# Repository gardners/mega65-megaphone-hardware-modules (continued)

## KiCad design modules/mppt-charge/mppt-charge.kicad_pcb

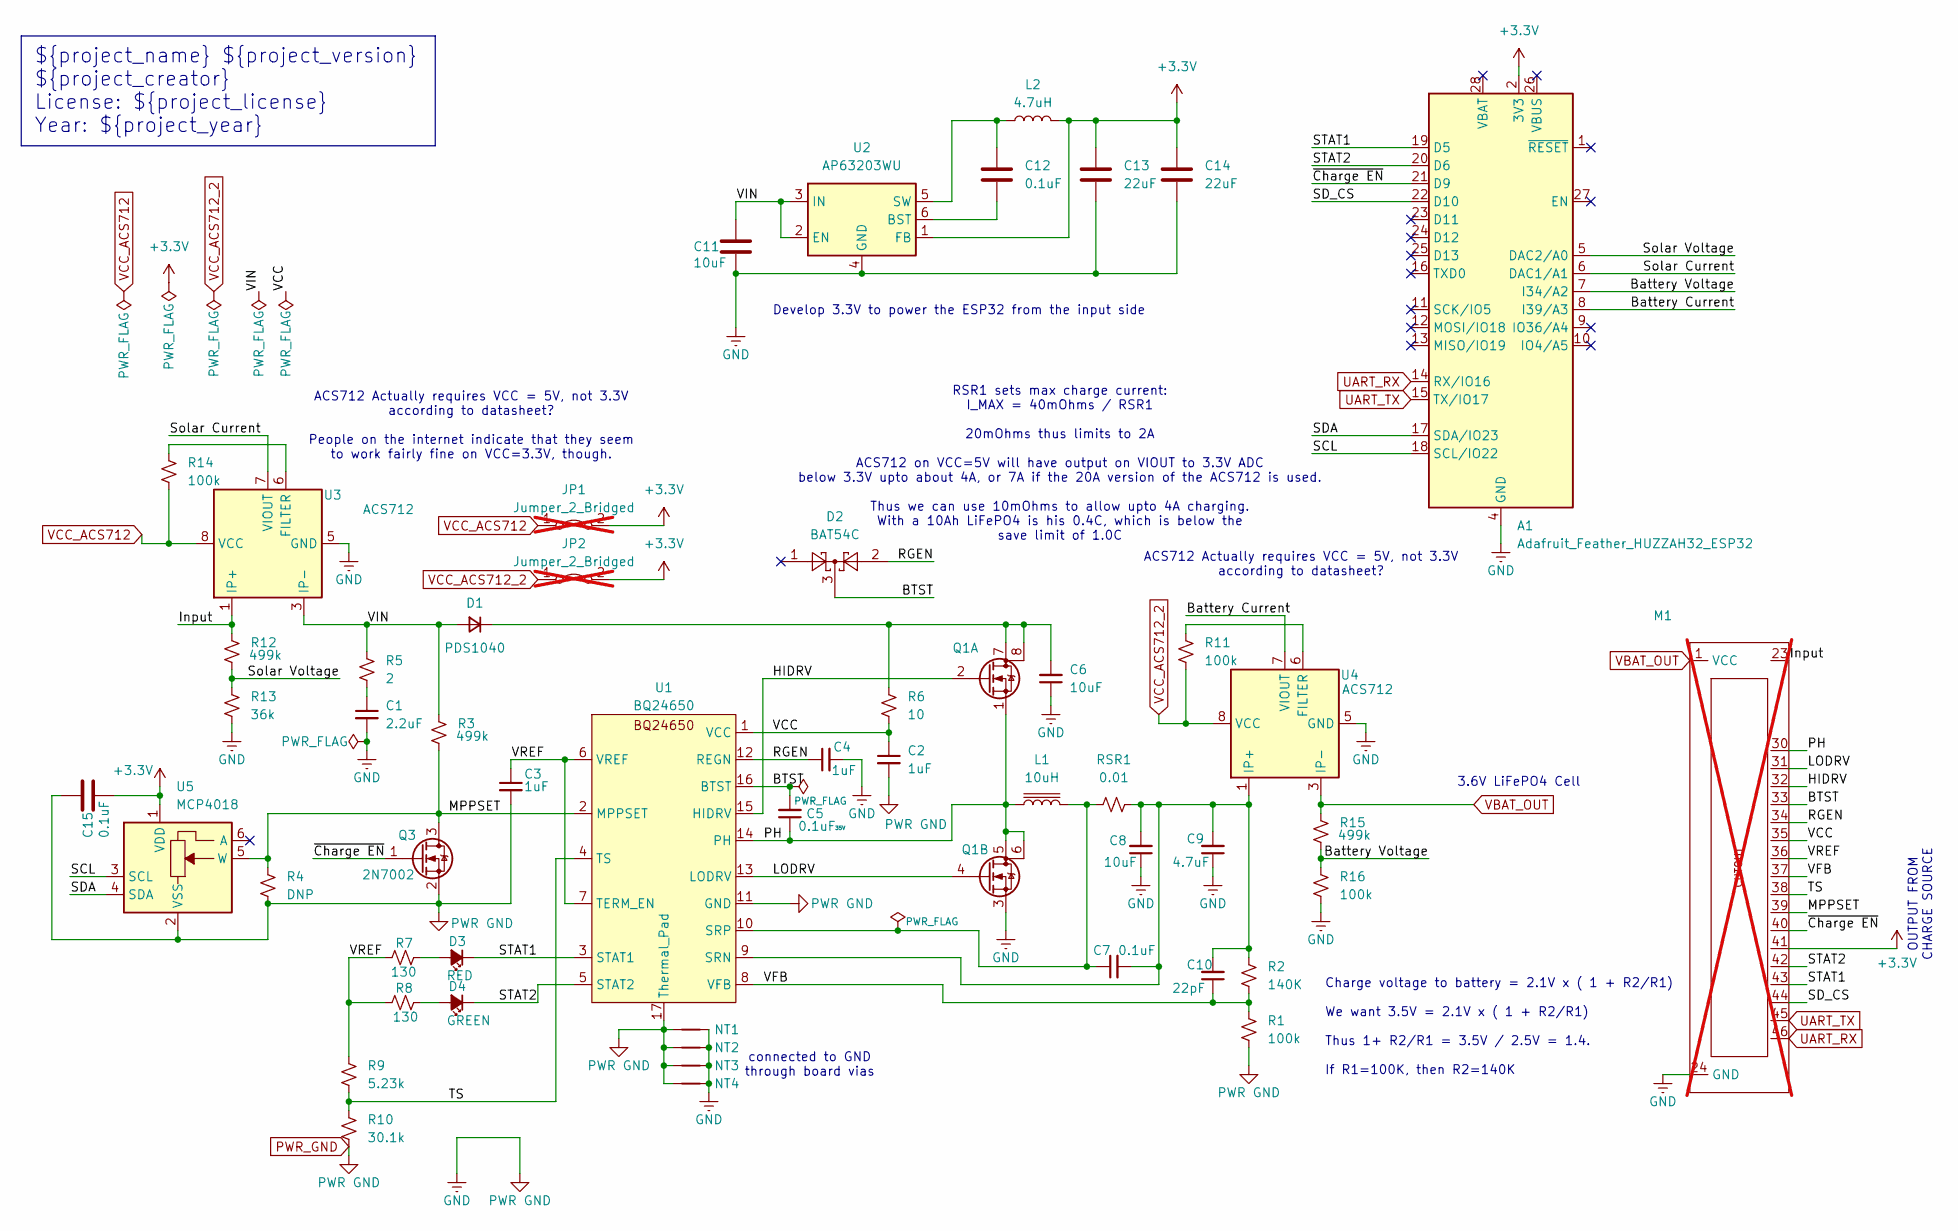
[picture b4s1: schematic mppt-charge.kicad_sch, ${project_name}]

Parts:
A1: Adafruit_Feather_HUZZAH32_ESP32; Adafruit_Feather; Mouser 485-4172
C1: 2.2uF; C_1210_3225Metric
C2, C3, C4: 1uF; C_0603_1608Metric
C5: 0.1uF; C_0603_1608Metric; Voltage Rating 35V
C6, C8: 10uF; C_1206_3216Metric
C7, C12, C15: 0.1uF; C_0603_1608Metric
C9: 4.7uF; C_0805_2012Metric
C10: 22pF; C_0603_1608Metric
C11: 10uF; C_0603_1608Metric
C13, C14: 22uF; C_0603_1608Metric; Mouser 621-PDS1040-13
D1: PDS1040; D_PowerDI-5; Mouser 583-BAT54C
D2: BAT54C; SOT-23; Mouser 583-BAT54C
D3: RED; LED_0603_1608Metric
D4: GREEN; LED_0603_1608Metric
JP1, JP2: Jumper_2_Bridged; SolderJumper-2_P1.3mm_Bridged_RoundedPad1.0x1.5mm; not fitted
L1: 10uH; L_Vishay_6.9x6.5; Mouser 70-IHLM2525CZER100M0
L2: 4.7uH; L_Vishay_IFSC-1515AH_4x4x1.8mm; Mouser 70-IFSC1515AHER4R7M0
M1: MegaCastle2x24-Module-I40.0x56.2-M80000307FFFC-SPAREPAD; not fitted
NT1, NT2, NT3, NT4: NetTie-2_SMD_Pad0.5mm
Q1: SI7272DP; PowerPAK_SO-8_Dual; Mouser 781-SI7272DP-GE3
Q3: 2N7002; SOT-23; Mouser 637-2N7002
R1, R11, R14, R16: 100k; R_0603_1608Metric
R2: 140K; R_0603_1608Metric
R3, R12, R15: 499k; R_0603_1608Metric
R4: DNP; R_0603_1608Metric
R5: 2; R_2512_6332Metric; Mouser 71-CRCW25122R00FKTG
R6: 10; R_0603_1608Metric
R7, R8: 130; R_0603_1608Metric
R9: 5.23k; R_0603_1608Metric
R10: 30.1k; R_0603_1608Metric
R13: 36k; R_0603_1608Metric
RSR1: 0.01; R_1206_3216Metric; Mouser 755-PMR18EZPFU10L0
U1: BQ24650; VQFN-16_EP_3.5x3.5_Pitch0.5mm; Mouser 595-BQ24650RVAR
U2: AP63203WU; TSOT-23-6; Mouser 621-AP63203QWU-7
U3, U4: ACS712; SOIC-8_3.9x4.9mm_P1.27mm; Mouser 250-71240LLCBTR010B3
U5: MCP4018; SOT-363_SC-70-6; Mouser 579-MCP4018T103ELTY

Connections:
+3.3V: A1.2 (3V3), C13.1, C14.1, C15.1, JP1.2 (B), JP2.2 (B), L2.2, M1.41, U2.1 (FB), U5.1 (VDD)
/BTST: C5.2, D2.3, M1.33, U1.16 (BTST)
/Battery Current: A1.8 (I39/A3), U4.7 (VIOUT)
/Battery Voltage: A1.7 (I34/A2), R15.2, R16.1
/HIDRV: M1.32, Q1.2 (G), U1.15 (HIDRV)
/Input: M1.23, R12.1, U3.1 (IP+), U3.2 (IP+)
/LODRV: M1.31, Q1.4 (G), U1.13 (LODRV)
/MPPSET: M1.39, Q3.3 (D), R3.2, R4.1, U1.2 (MPPSET), U5.5 (W)
/PH: C5.1, L1.1, M1.30, Q1.1 (S), Q1.5 (D), Q1.6 (D), U1.14 (PH)
/RGEN: C4.1, D2.2, M1.34, U1.12 (REGN)
/SCL: A1.18 (SCL/IO22), U5.3 (SCL)
/SDA: A1.17 (SDA/IO23), U5.4 (SDA)
/SD_CS: A1.22 (D10), M1.44
/STAT1: A1.19 (D5), D3.1 (K), M1.43, U1.3 (STAT1)
/STAT2: A1.20 (D6), D4.1 (K), M1.42, U1.5 (STAT2)
/Solar Current: A1.6 (DAC1/A1), U3.7 (VIOUT)
/Solar Voltage: A1.5 (DAC2/A0), R12.2, R13.1
/TS: M1.38, R9.2, R10.1, U1.4 (TS)
/VCC: C2.1, M1.35, R6.2, U1.1 (VCC)
/VFB: C10.1, M1.37, R1.1, R2.2, U1.8 (VFB)
/VIN: C11.2, D1.2 (A), R3.1, R5.1, U2.2 (EN), U2.3 (IN), U3.3 (IP-), U3.4 (IP-)
/VREF: C3.1, M1.36, R7.1, R8.1, R9.1, U1.6 (VREF), U1.7 (TERM_EN)
/~Charge EN: A1.21 (D9), M1.40, Q3.1 (G)
unnamed: C1.1, R5.2
unnamed: C6.2, D1.1 (K), Q1.7 (D), Q1.8 (D), R6.1
unnamed: D3.2 (A), R7.2
unnamed: D4.2 (A), R8.2
unnamed: C7.2, C8.2, C9.2, C10.2, R2.1, RSR1.1, U1.9 (SRN), U4.1 (IP+), U4.2 (IP+)
unnamed: C7.1, L1.2, RSR1.2, U1.10 (SRP)
unnamed: C12.2, U2.6 (BST)
unnamed: C12.1, L2.1, U2.5 (SW)
unnamed: R14.1, U3.6 (FILTER)
unnamed: R11.1, U4.6 (FILTER)
PWR_GND: A1.4 (GND), C1.2, C2.2, C3.2, C4.2, C6.1, C8.1, C9.1, C11.1, C13.2, C14.2, C15.2, M1.24 (GND), NT1.1, NT1.2, NT2.1, NT2.2, NT3.1, NT3.2, NT4.1, NT4.2, Q1.3 (S), Q3.2 (S), R1.2, R4.2, R10.2, R13.2, R16.2, U1.11 (GND), U1.17 (Thermal_Pad), U2.4 (GND), U3.5 (GND), U4.5 (GND), U5.2 (VSS)
UART_RX: A1.14 (RX/IO16), M1.46
UART_TX: A1.15 (TX/IO17), M1.45
VBAT_OUT: M1.1 (VCC), R15.1, U4.3 (IP-), U4.4 (IP-)
VCC_ACS712: JP1.1 (A), R14.2, U3.8 (VCC)
VCC_ACS712_2: JP2.1 (A), R11.2, U4.8 (VCC)

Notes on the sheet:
ACS712 Actually requires VCC = 5V, not 3.3V according to datasheet?
ACS712 Actually requires VCC = 5V, not 3.3V according to datasheet? People on the internet indicate that they seem to work fairly fine on VCC=3.3V, though.
3.6V LiFePO4 Cell
${project_name} ${project_version} ${project_creator} License: ${project_license} Year: ${project_year}
OUTPUT FROM CHARGE SOURCE
Charge voltage to battery = 2.1V x ( 1 + R2/R1) We want 3.5V = 2.1V x ( 1 + R2/R1) Thus 1+ R2/R1 = 3.5V / 2.5V = 1.4. If R1=100K, then R2=140K
RSR1 sets max charge current: I_MAX = 40mOhms / RSR1 20mOhms thus limits to 2A ACS712 on VCC=5V will have output on VIOUT to 3.3V ADC below 3.3V upto about 4A, or 7A if the 20A version of the ACS712 is used. Thus we can use 10mOhms to allow upto 4A charging. With a 10Ah LiFePO4 is his 0.4C, which i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
connected to GND through board vias
Develop 3.3V to power the ESP32 from the input side

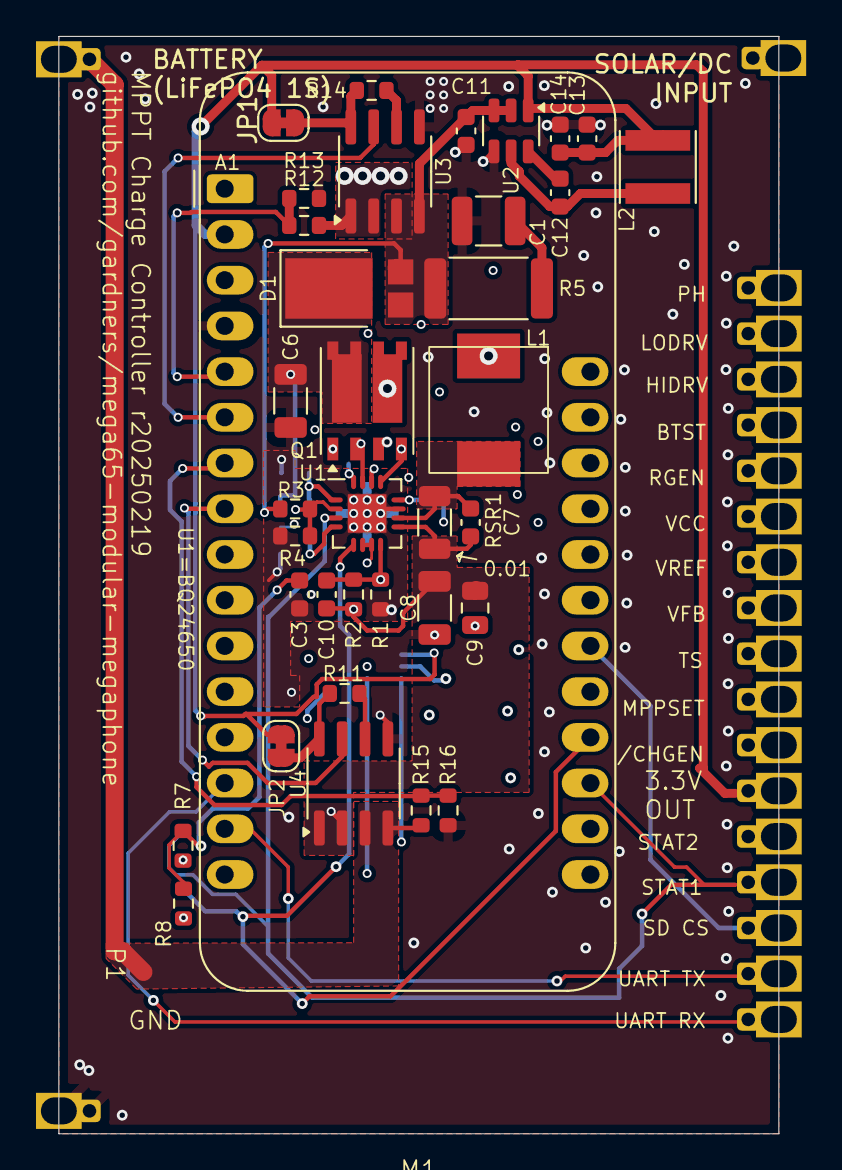
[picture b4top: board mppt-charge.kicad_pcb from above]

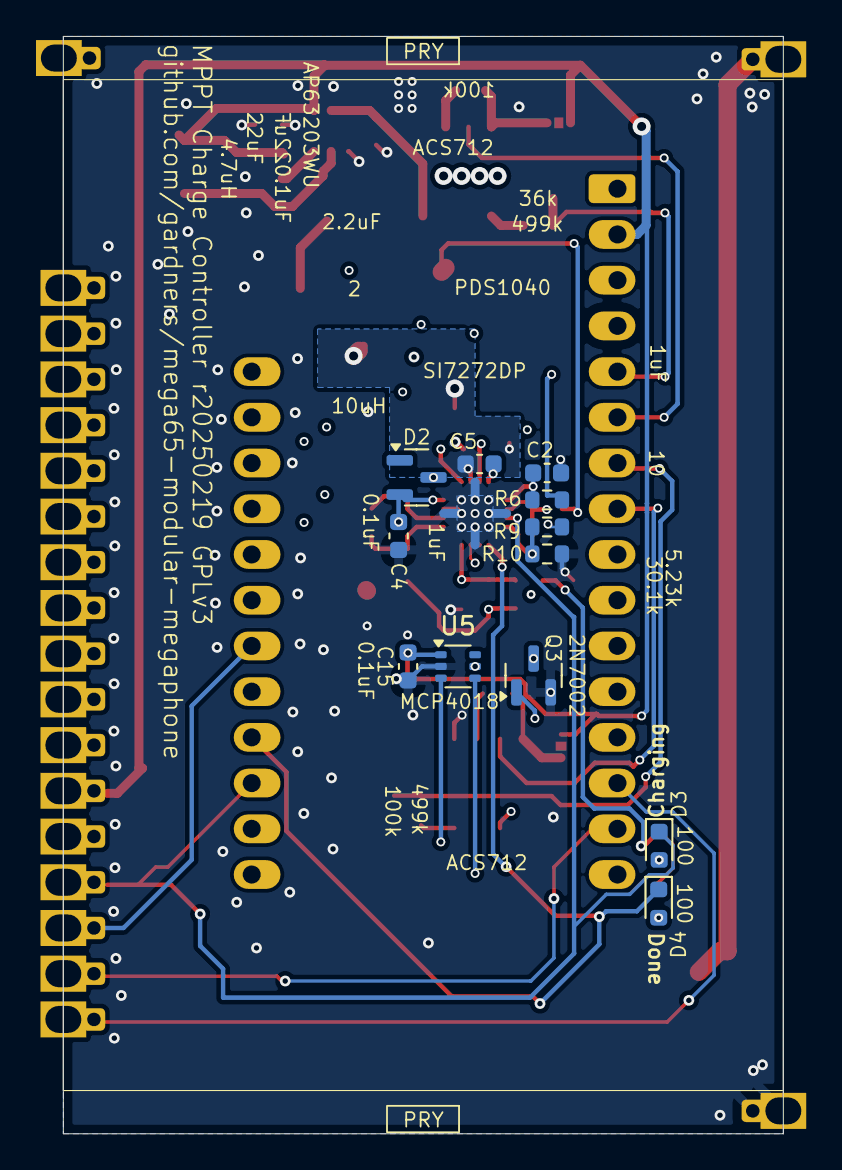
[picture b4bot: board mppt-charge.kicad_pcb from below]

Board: 4 copper layers, 40.0 x 61.0 mm, 53 parts (16 on the bottom side), 39 nets.

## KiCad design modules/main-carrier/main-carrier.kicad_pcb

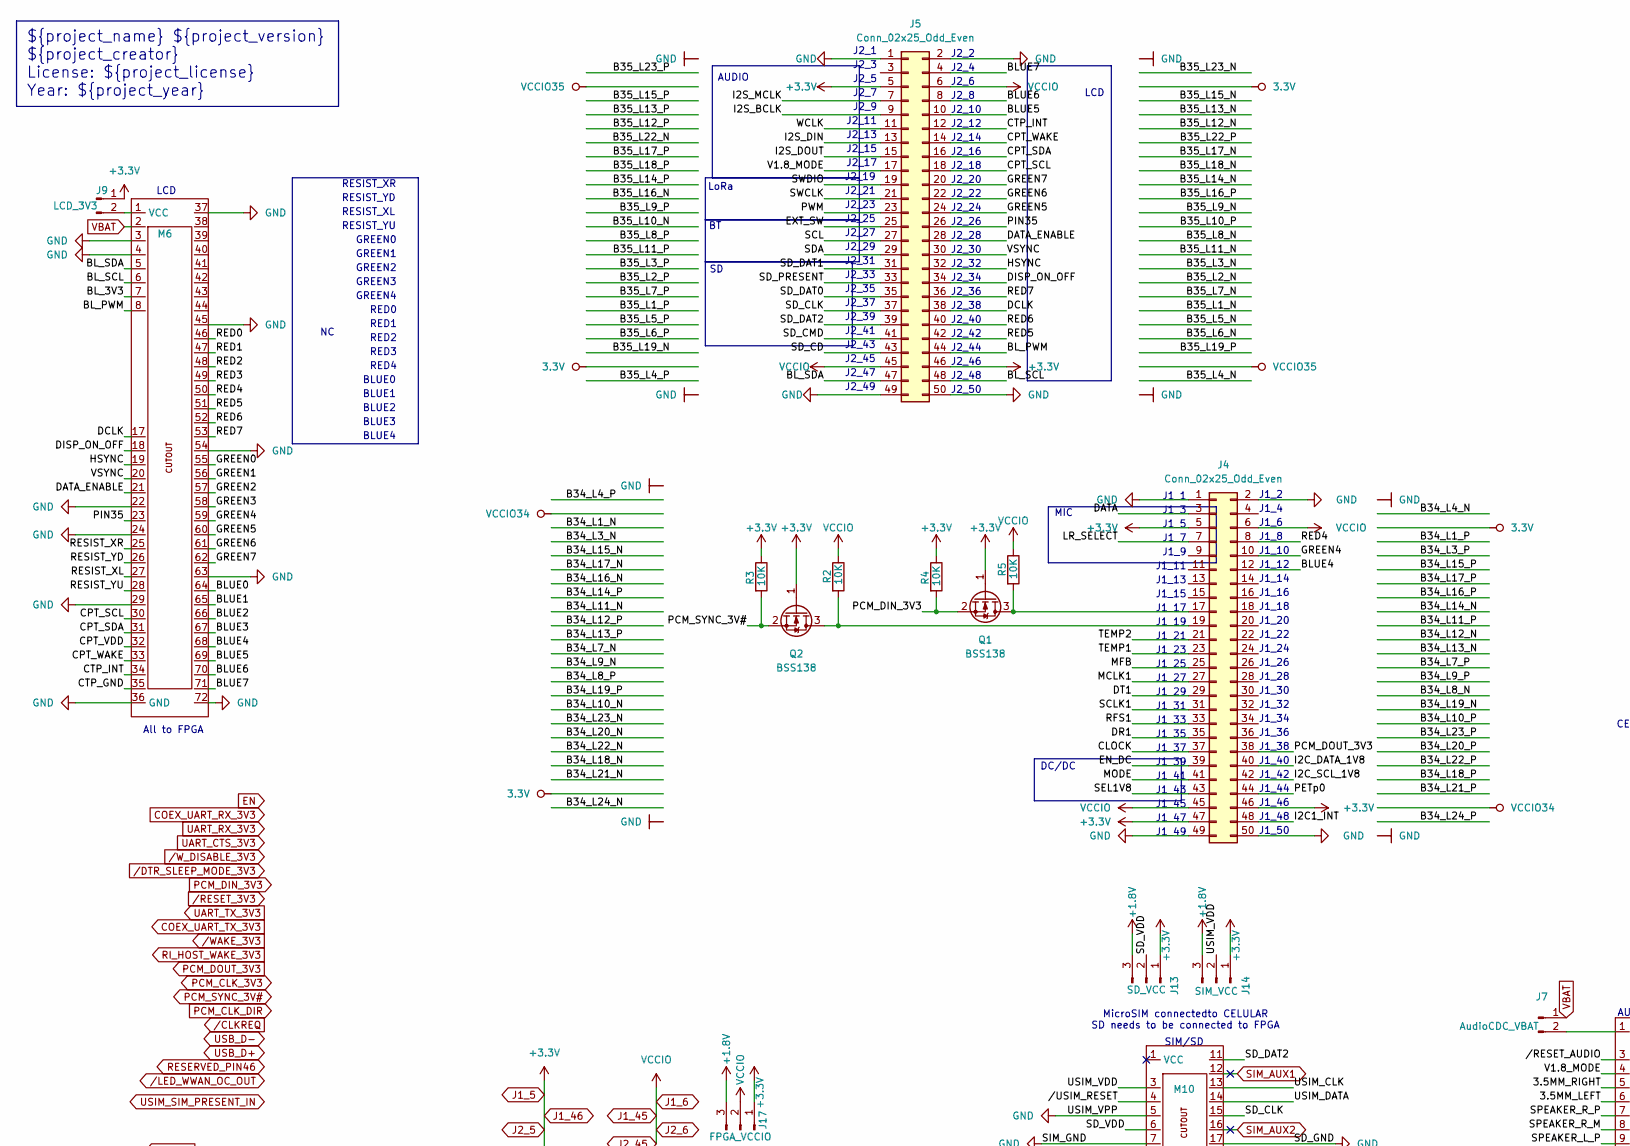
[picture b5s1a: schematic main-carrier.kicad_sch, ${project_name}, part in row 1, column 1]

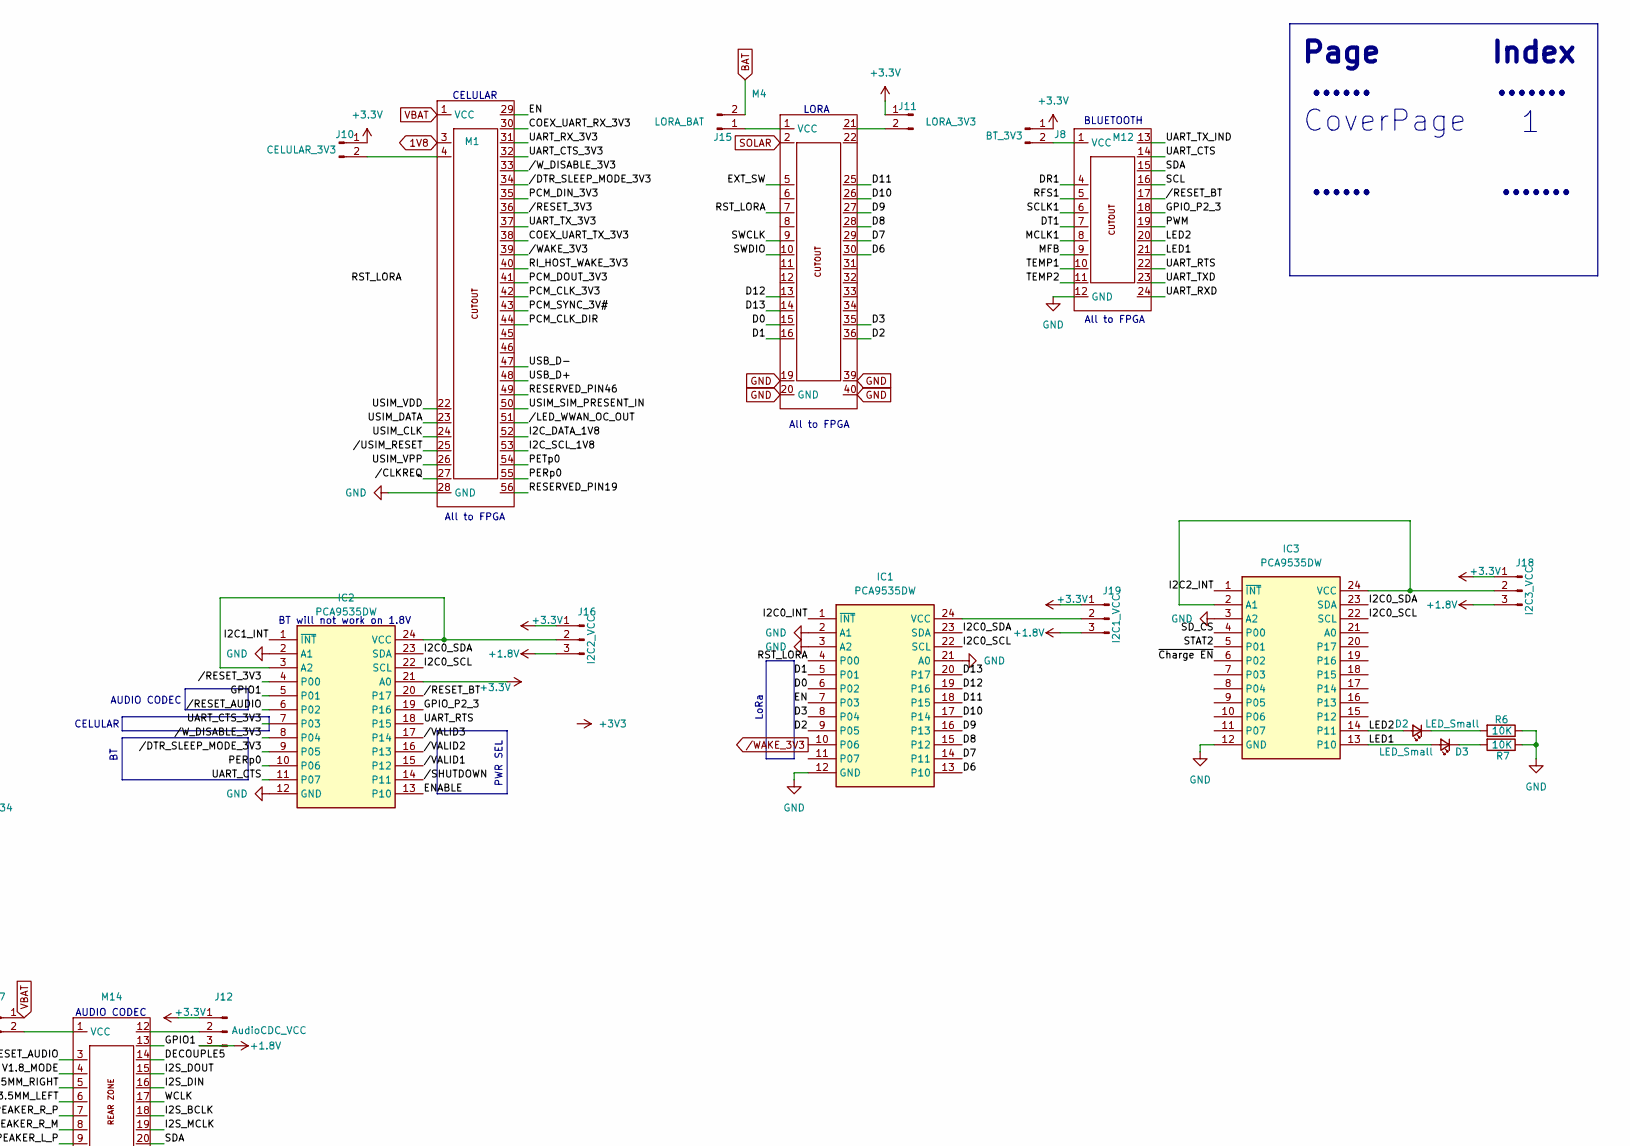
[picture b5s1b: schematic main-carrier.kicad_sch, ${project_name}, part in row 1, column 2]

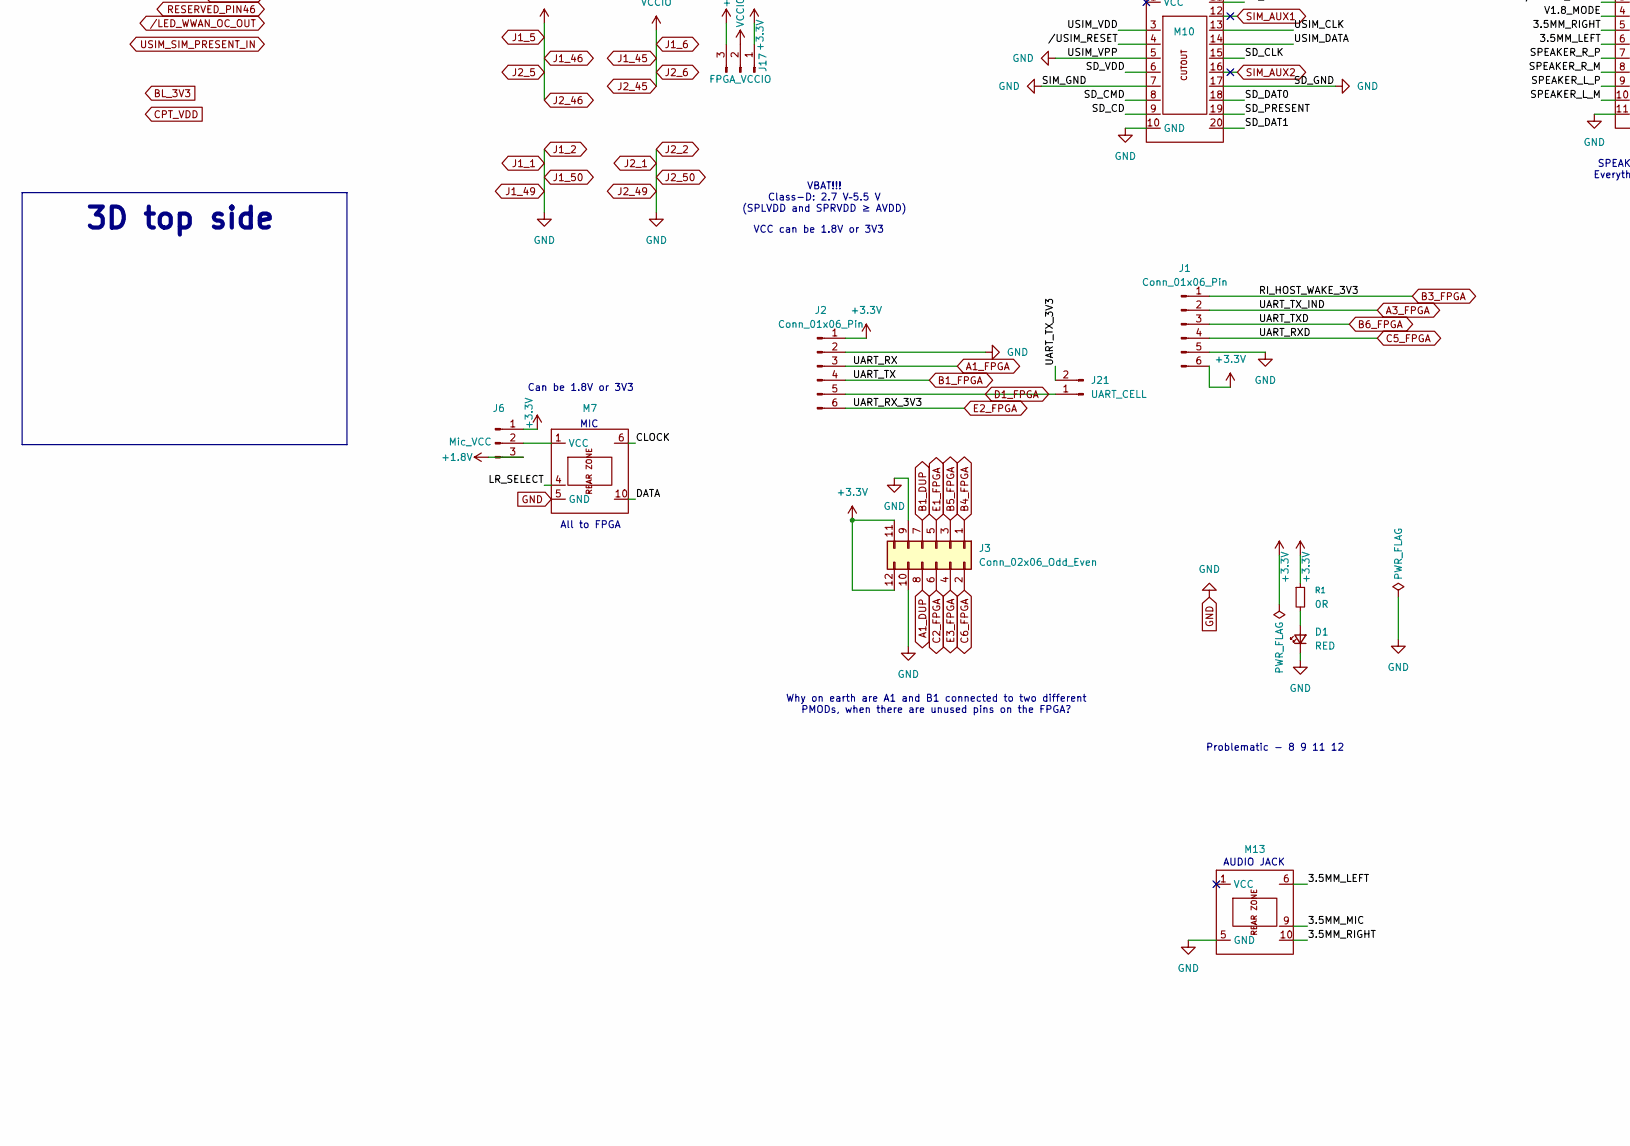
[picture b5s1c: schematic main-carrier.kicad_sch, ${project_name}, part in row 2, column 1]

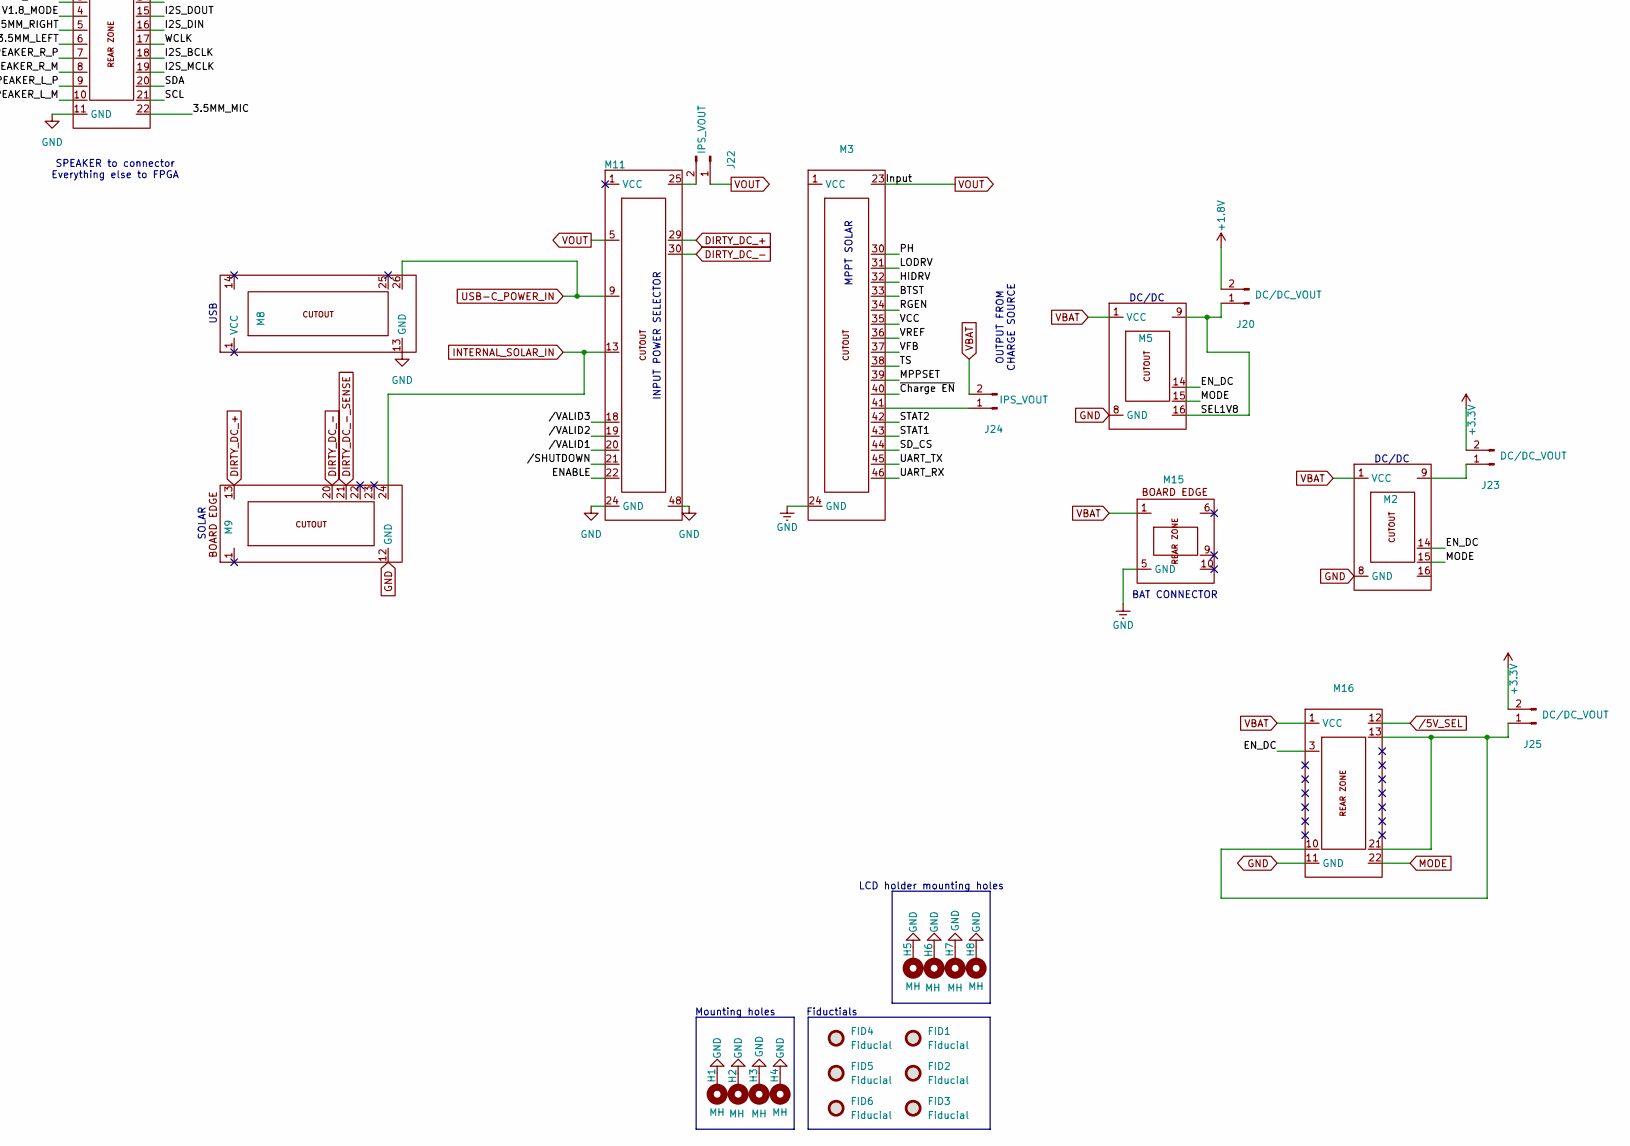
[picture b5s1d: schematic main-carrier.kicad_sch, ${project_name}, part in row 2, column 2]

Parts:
D1: RED; LED_0603_1608Metric; LCSC C965799
D2, D3: LED_Small; LED_0603_1608Metric
FID1, FID2, FID3, FID4, FID5, FID6: Fiducial; Fiducial_0.5mm_Mask1mm
H1, H2, H3, H4, H5, H6, H7, H8: MH; MountingHole_3mm_Pad
IC1, IC2, IC3: PCA9535DW; SOIC127P1030X265-24N; Mouser Part Number 595-PCA9535DW
J1, J2: Conn_01x06_Pin; PinHeader_1x06_P2.54mm_Vertical
J3: Conn_02x06_Odd_Even; PinHeader_2x06_P2.54mm_Vertical
J4, J5: Conn_02x25_Odd_Even; PinHeader_2x25_P2.54mm_Vertical
J6: Mic_VCC; PinSocket_1x03_P2.54mm_Vertical
J7: AudioCDC_VBAT; PinSocket_1x02_P2.54mm_Vertical
J8: BT_3V3; PinSocket_1x02_P2.54mm_Vertical
J9: LCD_3V3; PinSocket_1x02_P2.54mm_Vertical
J10: CELULAR_3V3; PinSocket_1x02_P2.54mm_Vertical
J11: LORA_3V3; PinSocket_1x02_P2.54mm_Vertical
J12: AudioCDC_VCC; PinSocket_1x03_P2.54mm_Vertical
J13: SD_VCC; PinSocket_1x03_P2.54mm_Vertical
J14: SIM_VCC; PinSocket_1x03_P2.54mm_Vertical
J15: LORA_BAT; PinSocket_1x02_P2.54mm_Vertical
J16: I2C2_VCC; PinSocket_1x03_P2.54mm_Vertical
J17: FPGA_VCCIO; PinSocket_1x03_P2.54mm_Vertical
J18: I2C3_VCC; PinSocket_1x03_P2.54mm_Vertical
J19: I2C1_VCC; PinSocket_1x03_P2.54mm_Vertical
J20, J23, J25: DC/DC_VOUT; PinSocket_1x02_P2.54mm_Vertical
J21: UART_CELL; PinSocket_1x02_P2.54mm_Vertical
J22, J24: IPS_VOUT; PinSocket_1x02_P2.54mm_Vertical
M1: MegaCastle2x28-I42.8x66.3-MB00007FFFFFFFF
M2, M5: MegaCastle2x8-I15.0x15.5-M8187
M3: MegaCastle2x24-I40.0x56.2-M80000307FFFC
M4: MegaCastle2x20-I40.0x46.0-MBCFFF3CFFF3
M6: MegaCastle2x36-I40.0x86.6-MFFFFFFFFFFFFFF
M7: MegaCastle2x5-I10.0x7.9-M9C4
M8: MegaCastle2x13-I20.0x28.2-M800C00C
M9: MegaCastle2x12-I20.0x25.7-M80181F
M10: MegaCastle2x10-I16.0x20.6-MBFFFF
M11: MegaCastle2x24-I47.0x56.2-M88887D8C0001
M12: MegaCastle2x12-I24.0x25.7-M9FFFFF
M13: MegaCastle2x7-I15.0x13.0-M8314
M14: MegaCastle2x11-I22.0x23.1-MBFFFFC
M15: MegaCastle2x5-I15.0x7.9-M8CC
M16: MegaCastle2x11-I15.7x23.1-MA0780C-EDGE
Q1, Q2: BSS138; SOT-23
R1: 0R; C_0402_1005Metric; LCSC C106231
R2, R3, R4, R5, R6, R7: 10K; R_0603_1608Metric

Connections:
1V8: M1.3
+1.8V: J6.3, J12.3, J13.3, J14.3, J16.3, J17.3, J18.3, J19.3, J20.2
/3.5MM_LEFT: M13.6, M14.6
/3.5MM_MIC: M13.9, M14.22
/3.5MM_RIGHT: M13.10, M14.5
/BLUE0: M6.64
/BLUE1: M6.65
/BLUE2: M6.66
/BLUE3: M6.67
/BLUE4: J4.12, M6.68
/BLUE5: J5.10, M6.69
/BLUE6: J5.8, M6.70
/BLUE7: J5.4, M6.71
/BL_PWM: J5.44, M6.8
/BL_SCL: J5.48, M6.6
/BL_SDA: J5.47, M6.5
/BTST: M3.33
/CLOCK: J4.37, M7.6
/CPT_SCL: J5.18, M6.30
/CPT_SDA: J5.16, M6.31
/CPT_WAKE: J5.14, M6.33
/CTP_GND: M6.35
/CTP_INT: J5.12, M6.34
/D0: IC1.6 (P02), M4.15
/D1: IC1.5 (P01), M4.16
/D2: IC1.9 (P05), M4.36
/D3: IC1.8 (P04), M4.35
/D6: IC1.13 (P10), M4.30
/D7: IC1.14 (P11), M4.29
/D8: IC1.15 (P12), M4.28
/D9: IC1.16 (P13), M4.27
/D10: IC1.17 (P14), M4.26
/D11: IC1.18 (P15), M4.25
/D12: IC1.19 (P16), M4.13
/D13: IC1.20 (P17), M4.14
/DATA: J4.3, M7.10
/DATA_ENABLE: J5.28, M6.21
/DCLK: J5.38, M6.17
/DECOUPLE5: M14.14
/DISP_ON_OFF: J5.34, M6.18
/DR1: J4.35, M12.4
/DT1: J4.29, M12.7
/ENABLE: IC2.13 (P10), M11.22
/EN_DC: J4.39, M2.14, M5.14, M16.3
/EXT_SW: J5.25, M4.5
/GPIO1: IC2.5 (P01), M14.13
/GPIO_P2_3: IC2.19 (P16), M12.18
/GREEN0: M6.55
/GREEN1: M6.56
/GREEN2: M6.57
/GREEN3: M6.58
/GREEN4: J4.10, M6.59
/GREEN5: J5.24, M6.60
/GREEN6: J5.22, M6.61
/GREEN7: J5.20, M6.62
/HIDRV: M3.32
/HSYNC: J5.32, M6.19
/I2C0_INT: IC1.1 (~INT)
/I2C0_SCL: IC1.22 (SCL), IC2.22 (SCL), IC3.22 (SCL)
/I2C0_SDA: IC1.23 (SDA), IC2.23 (SDA), IC3.23 (SDA)
/I2C1_INT: IC2.1 (~INT), J4.48
/I2C2_INT: IC3.1 (~INT)
/I2C_DATA_1V8: J4.40, M1.52
/I2C_SCL_1V8: J4.42, M1.53
/I2S_BCLK: J5.9, M14.18
/I2S_DIN: J5.13, M14.16
/I2S_DOUT: J5.15, M14.15
/I2S_MCLK: J5.7, M14.19
/LED1: D3.2 (A), IC3.13 (P10), M12.21
/LED2: D2.2 (A), IC3.14 (P11), M12.20
/LODRV: M3.31
/LR_SELECT: J4.7, M7.4
/MCLK1: J4.27, M12.8
/MFB: J4.25, M12.9
/MPPSET: M3.39
/PERp0: IC2.10 (P06), M1.55
/PETp0: J4.44, M1.54
/PH: M3.30
/PIN35: J5.26, M6.23
/PWM: J5.23, M12.19
/RED0: M6.46
/RED1: M6.47
/RED2: M6.48
/RED3: M6.49
/RED4: J4.8, M6.50
/RED5: J5.42, M6.51
/RED6: J5.40, M6.52
/RED7: J5.36, M6.53
/RESERVED_PIN19: M1.56
/RESIST_XL: M6.27
/RESIST_XR: M6.25
/RESIST_YD: M6.26
/RESIST_YU: M6.28
/RFS1: J4.33, M12.5
/RGEN: M3.34
/RST_LORA: IC1.4 (P00), M4.7
/SCL: J5.27, M12.16, M14.21
/SCLK1: J4.31, M12.6
/SDA: J5.29, M12.15, M14.20
/SD_CD: J5.43, M10.9
/SD_CLK: J5.37, M10.15
/SD_CMD: J5.41, M10.8
/SD_CS: IC3.4 (P00), M3.44
/SD_DAT0: J5.35, M10.18
/SD_DAT1: J5.31, M10.20
/SD_DAT2: J5.39, M10.11
/SD_PRESENT: J5.33, M10.19
/SD_VDD: J13.2, M10.6
/SEL1V8: J4.43, J20.1, M5.9, M5.16
/SPEAKER_L_M: M14.10
/SPEAKER_L_P: M14.9
/SPEAKER_R_M: M14.8
/SPEAKER_R_P: M14.7
/STAT1: M3.43
/STAT2: IC3.5 (P01), M3.42
/SWCLK: J5.21, M4.9
/SWDIO: J5.19, M4.10
/TEMP1: J4.23, M12.10
/TEMP2: J4.21, M12.11
/TS: M3.38
/UART_CTS: IC2.11 (P07), M12.14
/UART_RTS: IC2.18 (P15), M12.22
/USIM_CLK: M1.24, M10.13
/USIM_DATA: M1.23, M10.14
/USIM_VDD: J14.2, M1.22, M10.3
/V1.8_MODE: J5.17, M14.4
/VCC: M3.35
/VFB: M3.37
/VREF: M3.36
/VSYNC: J5.30, M6.20
/WCLK: J5.11, M14.17
//RESET_AUDIO: IC2.6 (P02), M14.3
//RESET_BT: IC2.20 (P17), M12.17
//SHUTDOWN: IC2.14 (P11), M11.21
//USIM_RESET: M1.25, M10.4
//VALID1: IC2.15 (P12), M11.20
//VALID2: IC2.16 (P13), M11.19
//VALID3: IC2.17 (P14), M11.18
/~Charge EN: IC3.6 (P02), M3.40
A1_DUP: J3.8
A1_FPGA: J2.3, M3.46
A3_FPGA: J1.2, M12.13
B1_DUP: J3.7
B1_FPGA: J2.4, M3.45
B3_FPGA: J1.1, M1.40
B4_FPGA: J3.1
B5_FPGA: J3.3
B6_FPGA: J1.3, M12.23
BAT: J15.2
BL_3V3: M6.7
C2_FPGA: J3.6
C5_FPGA: J1.4, M12.24
C6_FPGA: J3.2
COEX_UART_RX_3V3: M1.30
COEX_UART_TX_3V3: M1.38
CPT_VDD: M6.32
D1_FPGA: J2.5, J21.1
DIRTY_DC_+: M9.13, M11.29
DIRTY_DC_-: M9.20, M11.30
DIRTY_DC_-_SENSE: M9.21
E1_FPGA: J3.5
E2_FPGA: J2.6, M1.31
E3_FPGA: J3.4
EN: IC1.7 (P03), M1.29
GND: D1.1 (K), H1.1, H2.1, H3.1, H4.1, H5.1, H6.1, H7.1, H8.1, IC1.2 (A1), IC1.3 (A2), IC1.12 (GND), IC1.21 (A0), IC2.2 (A1), IC2.12 (GND), IC3.3 (A2), IC3.12 (GND), J1.5, J2.2, J3.9, J3.10, J4.1, J4.2, J4.49, J4.50, J5.1, J5.2, J5.49, J5.50, M1.26, M1.28 (GND), M2.8 (GND), M3.24 (GND), M4.19, M4.20 (GND), M4.39, M4.40, M5.8 (GND), M6.3, M6.4, M6.22, M6.24, M6.29, M6.36 (GND), M6.37, M6.45, M6.54, M6.63, M6.72, M7.5 (GND), M8.13 (GND), M9.12 (GND), M10.5, M10.7, M10.10 (GND), M10.17, M11.24 (GND), M11.48, M12.12 (GND), M13.5 (GND), M14.11 (GND), M15.5 (GND), M16.11 (GND), R6.1, R7.1
INTERNAL_SOLAR_IN: M9.24, M11.13
J1_45: J4.6, J4.45, J5.6, J5.45, J17.2, R2.1, R5.1
J1_46: IC2.21 (A0), J1.6, J2.1, J3.11, J3.12, J4.5, J4.46, J4.47, J5.5, J5.46, J6.1, J8.1, J9.1, J10.1, J11.1, J12.1, J13.1, J14.1, J16.1, J17.1, J18.1, J19.1, J23.2, J25.2, Q1.1 (G), Q2.1 (G), R1.1, R3.1, R4.1
MODE: J4.41, M2.15, M5.15, M16.22
unnamed: D1.2 (A), R1.2
unnamed: D2.1 (K), R6.2
unnamed: D3.1 (K), R7.2
unnamed: IC1.24 (VCC), J19.2
unnamed: IC2.3 (A2), IC2.24 (VCC), J16.2
unnamed: IC3.2 (A1), IC3.24 (VCC), J18.2
unnamed: J4.17, Q1.3 (D), R5.2
unnamed: J4.19, Q2.3 (D), R2.2
unnamed: J6.2, M7.1 (VCC)
unnamed: J7.2, M14.1 (VCC)
unnamed: J8.2, M12.1 (VCC)
unnamed: J9.2, M6.1 (VCC)
unnamed: J10.2, M1.4
unnamed: J11.2, M4.21
unnamed: J12.2, M14.12
unnamed: J15.1, M4.1 (VCC)
unnamed: J22.2, M11.25
unnamed: J23.1, M2.9
unnamed: J24.1, M3.41
unnamed: J25.1, M16.10, M16.13, M16.21
PCM_CLK_3V3: M1.42
PCM_CLK_DIR: M1.44
PCM_DIN_3V3: M1.35, Q1.2 (S), R4.2
PCM_DOUT_3V3: J4.38, M1.41
PCM_SYNC_3V#: M1.43, Q2.2 (S), R3.2
RESERVED_PIN46: M1.49
SIM_AUX1: M10.12
SIM_AUX2: M10.16
SOLAR: M4.2
UART_CTS_3V3: IC2.7 (P03), M1.32
UART_TX_3V3: J21.2, M1.37
USB-C_POWER_IN: M8.26, M11.9
USB_D+: M1.48
USB_D-: M1.47
USIM_SIM_PRESENT_IN: M1.50
VBAT: J7.1, J24.2, M1.1 (VCC), M2.1 (VCC), M5.1 (VCC), M6.2, M15.1, M16.1 (VCC)
VOUT: J22.1, M3.23, M11.5
/5V_SEL: M16.12
/CLKREQ: M1.27
/DTR_SLEEP_MODE_3V3: IC2.9 (P05), M1.34
/LED_WWAN_OC_OUT: M1.51
/RESET_3V3: IC2.4 (P00), M1.36
/WAKE_3V3: IC1.10 (P06), M1.39
/W_DISABLE_3V3: IC2.8 (P04), M1.33

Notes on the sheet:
J1_31
J1_17
J1_19
SPEAKER to connector Everything else to FPGA
AUDIO CODEC
INPUT POWER SELECTOR
J1_33
J1_24
J2_47
J1_11
RED3
J1_44
J1_21
Fiductials
BLUE3
J2_1
J2_35
SOLAR
J1_50
LoRa
BLUE0
J1_5
GREEN0
Problematic - 8 9 11 12
J2_43
PWR SEL
All to FPGA
J2_48
GREEN3
DC/DC
J1_7
J2_45
MIC
3D top side
J2_4
J1_18
J1_49
J1_15
J2_37
J1_26

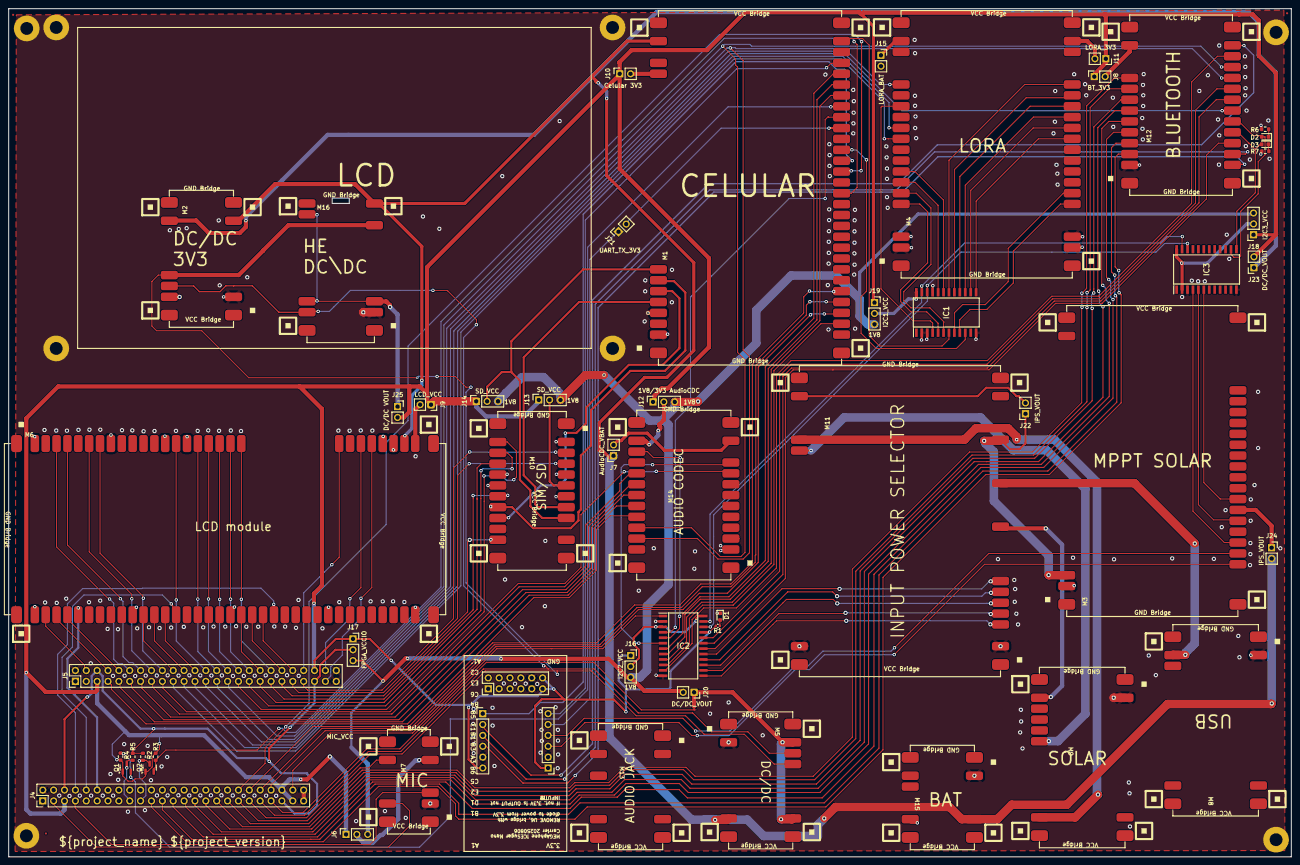
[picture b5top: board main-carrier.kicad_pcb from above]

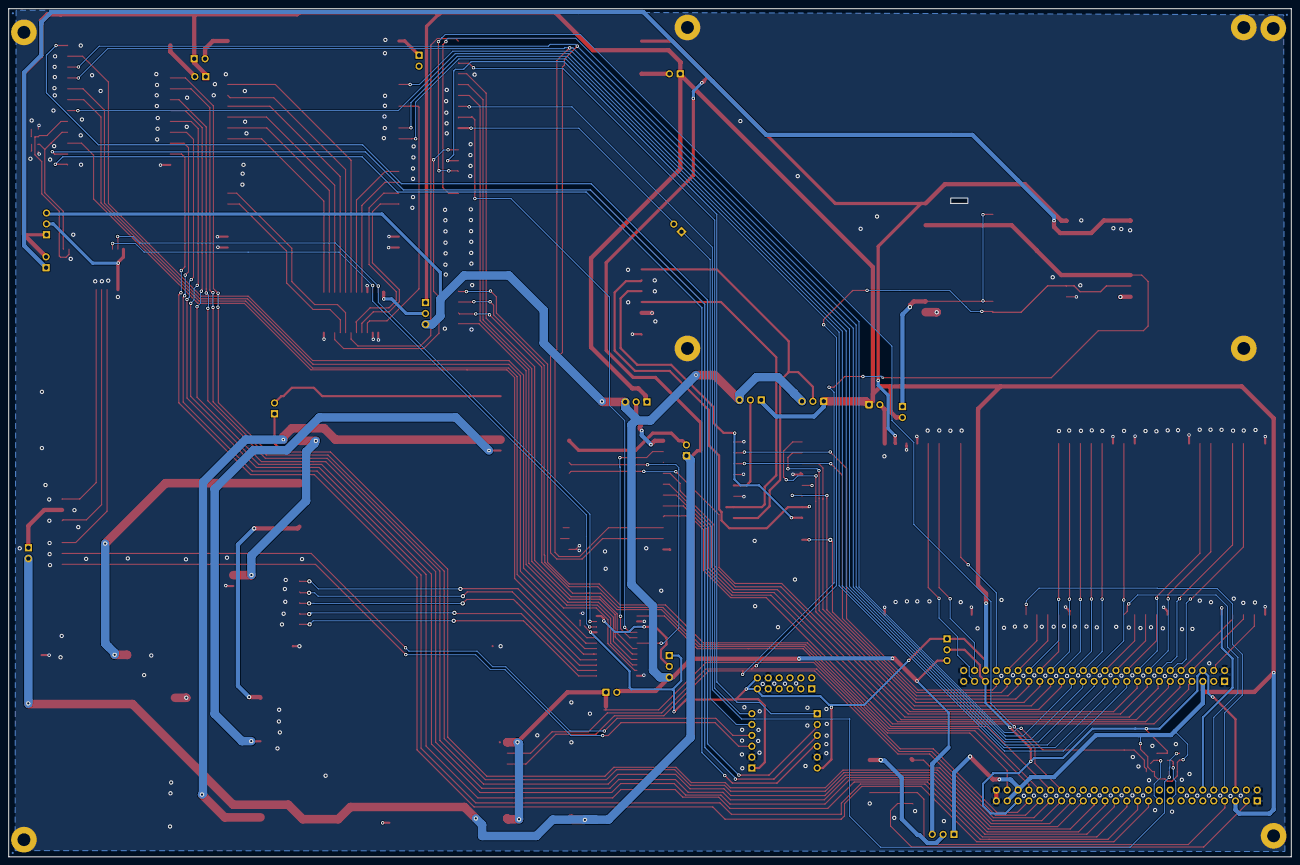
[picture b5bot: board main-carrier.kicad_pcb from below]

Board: 4 copper layers, 299.7 x 198.2 mm, 70 parts (3 on the bottom side), 147 nets.
